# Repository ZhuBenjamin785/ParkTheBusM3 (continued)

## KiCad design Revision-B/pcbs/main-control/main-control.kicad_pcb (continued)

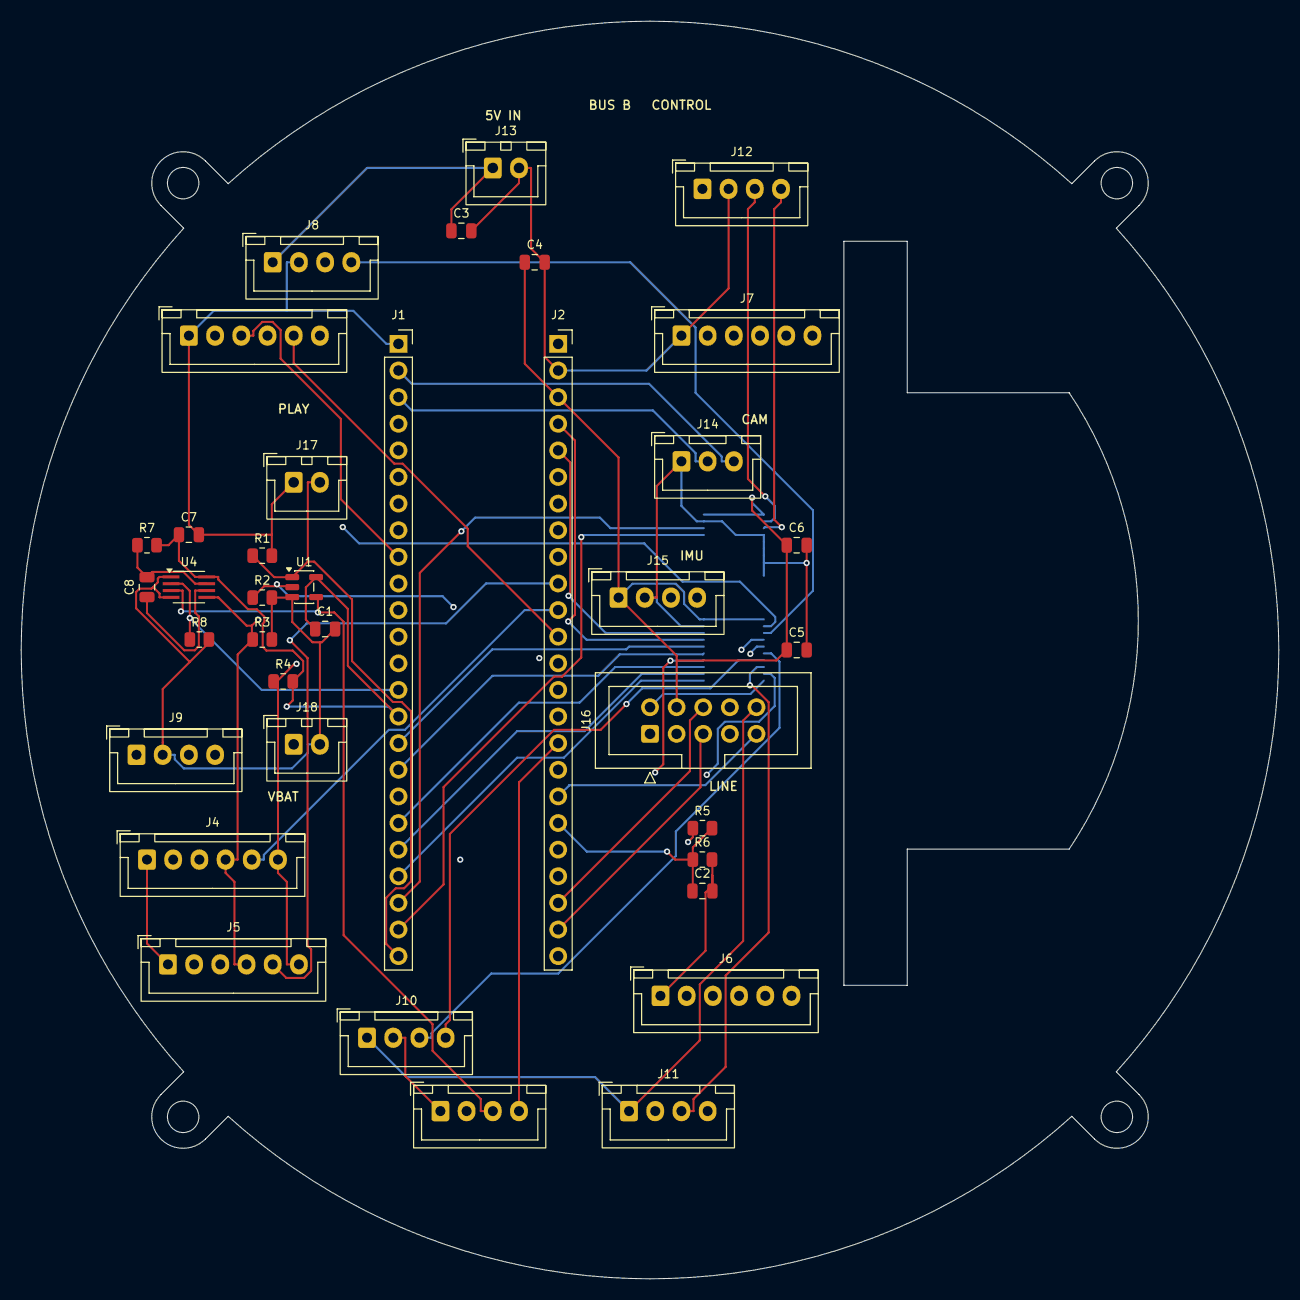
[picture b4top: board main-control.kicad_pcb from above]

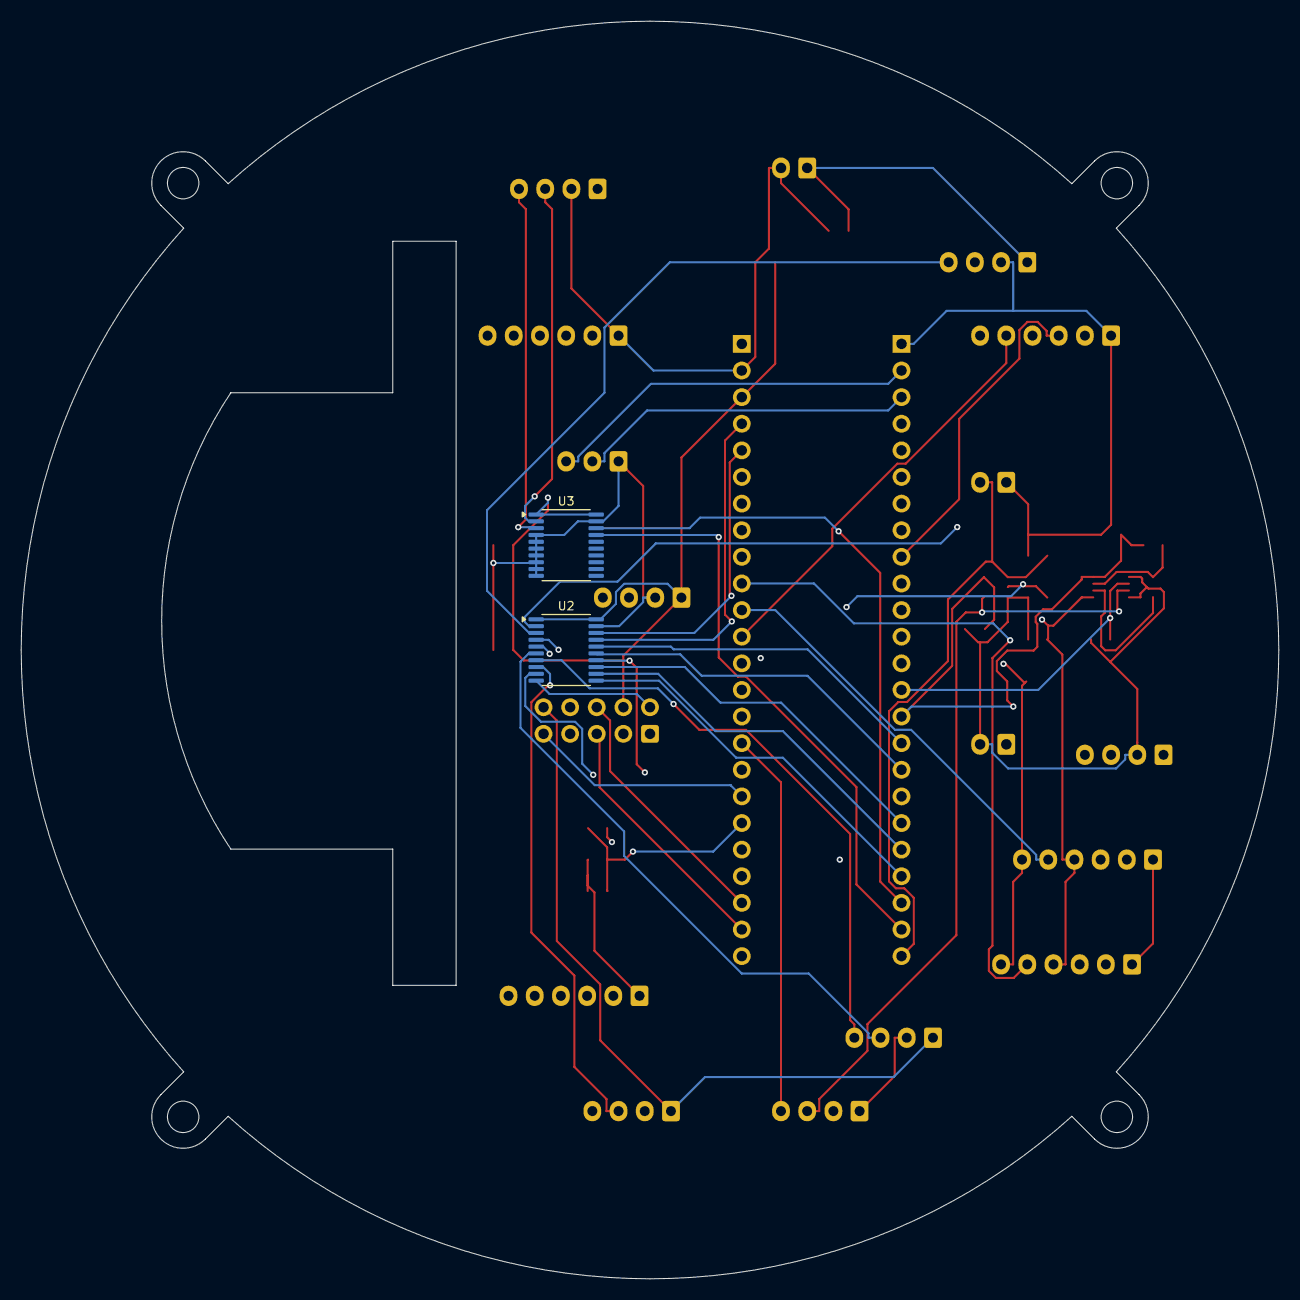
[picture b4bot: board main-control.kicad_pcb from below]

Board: 4 copper layers, 120.0 x 120.0 mm, 43 parts (2 on the bottom side), 59 nets.

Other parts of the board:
H1, H2, H3, H4: NPTH 3.0

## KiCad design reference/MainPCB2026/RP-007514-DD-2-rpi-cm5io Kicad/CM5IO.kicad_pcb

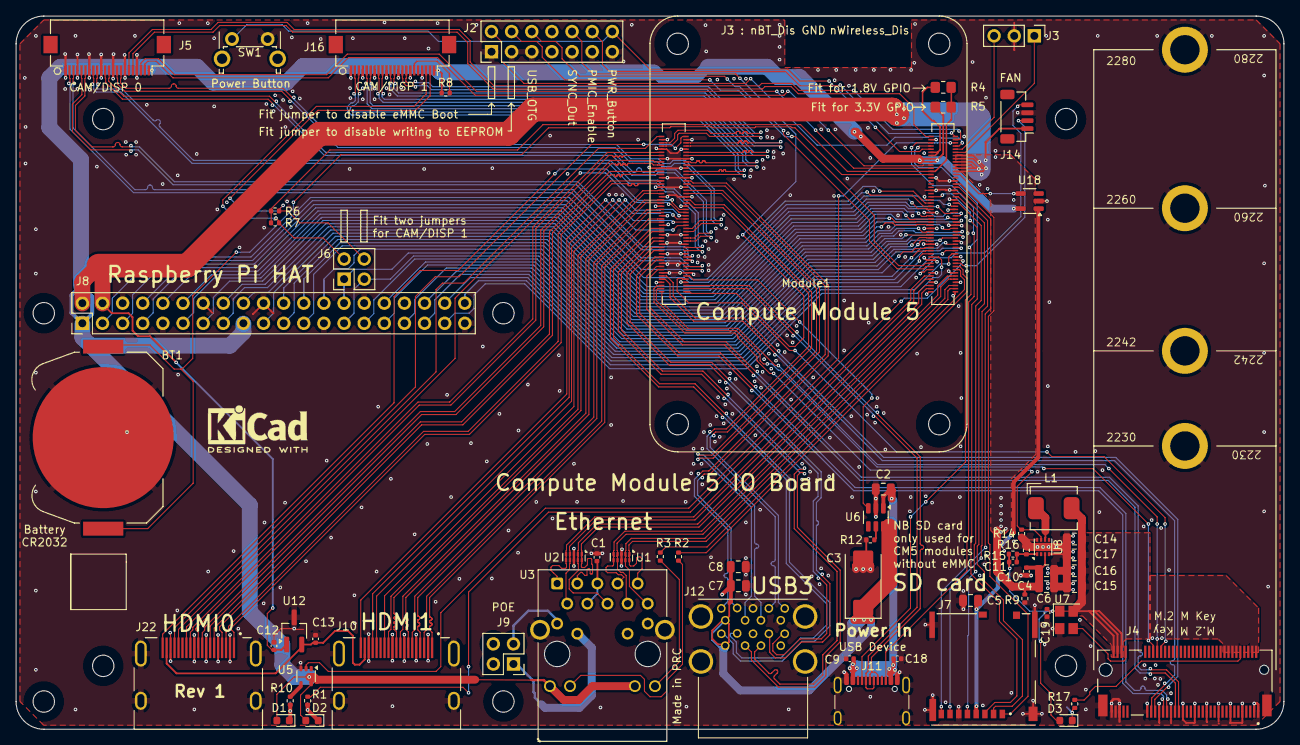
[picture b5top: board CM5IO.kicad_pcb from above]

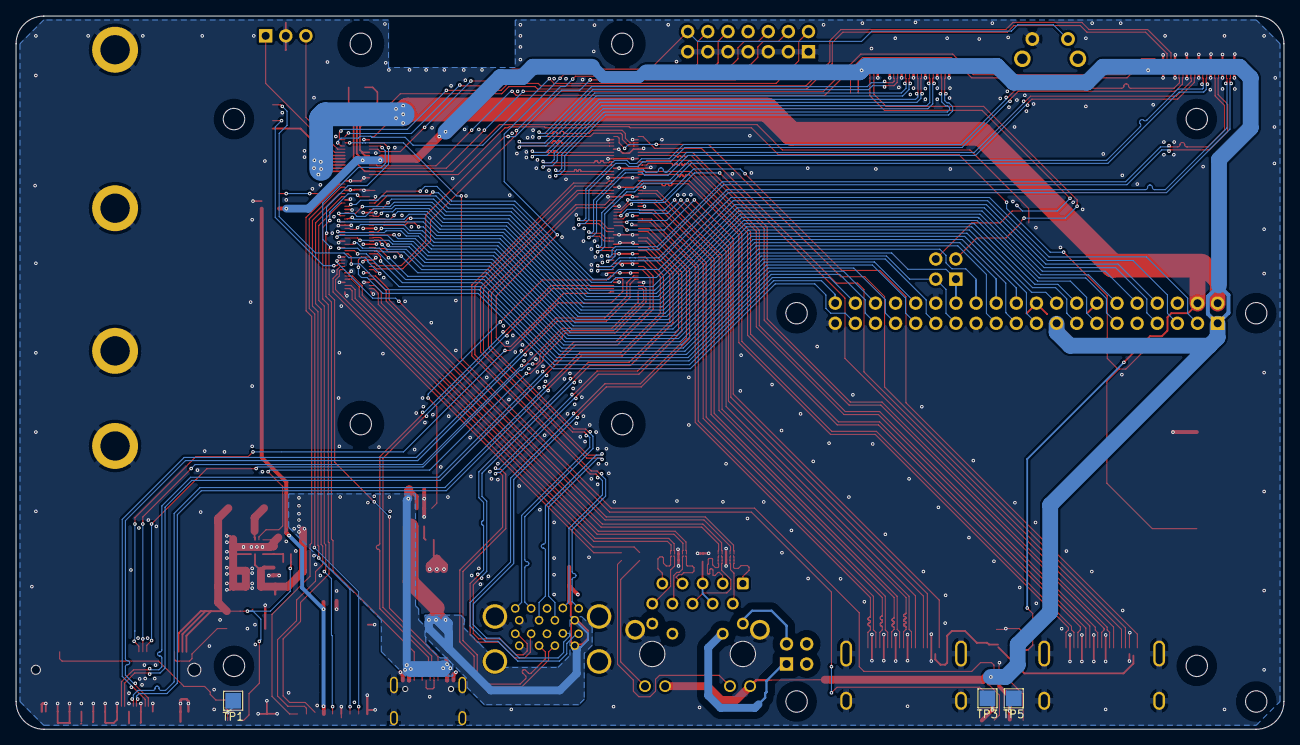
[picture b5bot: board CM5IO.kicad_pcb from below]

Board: 4 copper layers, 160.0 x 90.0 mm, 76 parts (3 on the bottom side), 161 nets.

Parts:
BT1: Battery_Cell; BatteryHolder_Keystone_3034_1x20mm
C1, C9, C10, C12, C13, C18, C19: 100n; C_0402_1005Metric
C2, C4, C5, C6, C7, C8, C14, C15, C16, C17: 10u; C_0805_2012Metric
C3: 100uF; CP_EIA-7343-31_Kemet-D
C11: 4.7nF; C_0402_1005Metric
D1: LED Red; LED_0603_1608Metric
D2, D3: LED Green; LED_0603_1608Metric
H1, H2, H3, H4, H5, H6, H7, H8: MountingHole; MountingHole_2.7mm_M2.5_DIN965
J2: Conn_02x07_Odd_Even; PinHeader_2x07_P2.54mm_Vertical
J3: Conn_01x03; PinHeader_1x03_P2.54mm_Vertical
J4: Bus_M.2_Socket_M; M.2 M Key socket
J5, J16: Conn_01x22_Female; Hirose_FH12-22S-0.5SH_1x22-1MP_P0.50mm_Horizontal
J6, J9: THD-02-R; PinHeader_2x02_P2.54mm_Vertical
J7: Micro_SD_Card_Det; SDCARD_MOLEX_503398-1892
J8: THD-20-R; PinHeader_2x20_P2.54mm_Vertical
J10, J22: 690-019-298-412; EDAC 690-019-298-412
J11: USB_C_Receptacle_USB2.0; USB_C_Receptacle_GCT_USB4105-xx-A_16P_TopMnt_Horizontal
J12: USB3_A; MTCONN_UBAF30-D2011
J14: JST_SHBM04B-SRSS-TB; JST_SH_BM04B-SRSS-TB_1x04-1MP_P1.00mm_Vertical
L1: 2.2uH; L_Bourns_SRP5030CC
Module1: ComputeModule5-CM5; Raspberry-Pi-5-Compute-Module
R1, R10, R17: 1k; R_0402_1005Metric
R2, R3: 470R; R_0402_1005Metric
R4: nf; R_0805_2012Metric_Pad1.20x1.40mm_HandSolder
R5: 0R; R_0805_2012Metric_Pad1.20x1.40mm_HandSolder
R6, R7, R8, R9, R16: 2.2K 1%; R_0402_1005Metric
R12: 15K 1%; R_0402_1005Metric
R14: 100K 1%; R_0402_1005Metric
R15: 10K 1%; R_0402_1005Metric
SW1: Right angle Tact button; SW_Tactile_SPST_Angled_PTS645Vx58-2LFS
TP1, TP3, TP5: TestPoint; TestPoint_Pad_2.0x2.0mm
U1, U2: TPD4EUSB30; USON-10_2.5x1.0mm_P0.5mm
U3: MagJack-A70-112-331N126; TRJG0926HENL
U5: 74LVC1G07SE-7; SOT-353_SC-70-5
U6: AP22653W6; SOT-23-6
U7: ASEK-32.768KHZ-L-R-T; Crystal_SMD_3225-4Pin_3.2x2.5mm
U8: AP3441SHE-7B; DFN-8-1EP_2x2mm_P0.5mm_EP1.05x1.75mm
U12: RT9742SNGV; TSOT-23_HandSoldering
U18: RT9742GGJ5; SOT-23-5
logo1: KiCad-Logo2_5mm_SilkScreen

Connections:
/+3.3v: D1.2 (A), D2.2 (A), J5.22, J8.1, J8.17, J16.22, Module1.84 (+3.3v_(Output)), Module1.86 (+3.3v_(Output)), R5.1, R8.1, U3.15 (LEDY_A), U3.17 (LEDG_A), U5.5 (VCC), U18.5 (IN)
/+5v: C2.1, C4.1, C6.1, C9.1, C10.1, C12.1, C18.1, J8.2, J8.4, J11.A4 (VBUS), J11.A9 (VBUS), J11.B4 (VBUS), J11.B9 (VBUS), J14.1, Module1.77 (+5v_(Input)), Module1.79 (+5v_(Input)), Module1.81 (+5v_(Input)), Module1.83 (+5v_(Input)), Module1.85 (+5v_(Input)), Module1.87 (+5v_(Input)), R9.1, U6.1 (IN), U8.3 (VIN), U12.1 (IN)
/CC1: J11.A5 (CC1), Module1.94 (CC1)
/CC2: J11.B5 (CC2), Module1.96 (CC2)
/CM5_GPIO ( Ethernet, GPIO, SDCARD)/+1.8v: Module1.88 (+1.8v_(Output)), Module1.90 (+1.8v_(Output)), R4.1
/CM5_GPIO ( Ethernet, GPIO, SDCARD)/BT_nDis: J3.3, Module1.91 (BT_nDisable)
/CM5_GPIO ( Ethernet, GPIO, SDCARD)/CAM_GPIO0: J5.17, Module1.97 (CAM_GPIO0)
/CM5_GPIO ( Ethernet, GPIO, SDCARD)/CAM_GPIO1: J5.18, Module1.100 (CAM_GPIO1)
/CM5_GPIO ( Ethernet, GPIO, SDCARD)/EEPROM_nWP: J2.4, Module1.20 (EEPROM_nWP)
/CM5_GPIO ( Ethernet, GPIO, SDCARD)/ETH_LEDG: Module1.17 (Ethernet_nLED2(3.3v)), R2.2
/CM5_GPIO ( Ethernet, GPIO, SDCARD)/ETH_LEDY: Module1.15 (Ethernet_nLED3(3.3v)), R3.2
/CM5_GPIO ( Ethernet, GPIO, SDCARD)/GPIO2: J8.3, Module1.58 (GPIO2)
/CM5_GPIO ( Ethernet, GPIO, SDCARD)/GPIO3: J8.5, Module1.56 (GPIO3)
/CM5_GPIO ( Ethernet, GPIO, SDCARD)/GPIO4: J8.7, Module1.54 (GPIO4)
/CM5_GPIO ( Ethernet, GPIO, SDCARD)/GPIO5: J8.29, Module1.34 (GPIO5)
/CM5_GPIO ( Ethernet, GPIO, SDCARD)/GPIO6: J8.31, Module1.30 (GPIO6)
/CM5_GPIO ( Ethernet, GPIO, SDCARD)/GPIO7: J8.26, Module1.37 (GPIO7)
/CM5_GPIO ( Ethernet, GPIO, SDCARD)/GPIO8: J8.24, Module1.39 (GPIO8)
/CM5_GPIO ( Ethernet, GPIO, SDCARD)/GPIO9: J8.21, Module1.40 (GPIO9)
/CM5_GPIO ( Ethernet, GPIO, SDCARD)/GPIO10: J8.19, Module1.44 (GPIO10)
/CM5_GPIO ( Ethernet, GPIO, SDCARD)/GPIO11: J8.23, Module1.38 (GPIO11)
/CM5_GPIO ( Ethernet, GPIO, SDCARD)/GPIO12: J8.32, Module1.31 (GPIO12)
/CM5_GPIO ( Ethernet, GPIO, SDCARD)/GPIO13: J8.33, Module1.28 (GPIO13)
/CM5_GPIO ( Ethernet, GPIO, SDCARD)/GPIO14: J8.8, Module1.55 (GPIO14)
/CM5_GPIO ( Ethernet, GPIO, SDCARD)/GPIO15: J8.10, Module1.51 (GPIO15)
/CM5_GPIO ( Ethernet, GPIO, SDCARD)/GPIO16: J8.36, Module1.29 (GPIO16)
/CM5_GPIO ( Ethernet, GPIO, SDCARD)/GPIO17: J8.11, Module1.50 (GPIO17)
/CM5_GPIO ( Ethernet, GPIO, SDCARD)/GPIO18: J8.12, Module1.49 (GPIO18)
/CM5_GPIO ( Ethernet, GPIO, SDCARD)/GPIO19: J8.35, Module1.26 (GPIO19)
/CM5_GPIO ( Ethernet, GPIO, SDCARD)/GPIO20: J8.38, Module1.27 (GPIO20)
/CM5_GPIO ( Ethernet, GPIO, SDCARD)/GPIO21: J8.40, Module1.25 (GPIO21)
/CM5_GPIO ( Ethernet, GPIO, SDCARD)/GPIO22: J8.15, Module1.46 (GPIO22)
/CM5_GPIO ( Ethernet, GPIO, SDCARD)/GPIO23: J8.16, Module1.47 (GPIO23)
/CM5_GPIO ( Ethernet, GPIO, SDCARD)/GPIO24: J8.18, Module1.45 (GPIO24)
/CM5_GPIO ( Ethernet, GPIO, SDCARD)/GPIO25: J8.22, Module1.41 (GPIO25)
/CM5_GPIO ( Ethernet, GPIO, SDCARD)/GPIO26: J8.37, Module1.24 (GPIO26)
/CM5_GPIO ( Ethernet, GPIO, SDCARD)/GPIO27: J8.13, Module1.48 (GPIO27)
/CM5_GPIO ( Ethernet, GPIO, SDCARD)/GPIO_VREF: Module1.78 (GPIO_VREF(1.8v/3.3v_Input)), R4.2, R5.2, R6.1, R7.1
/CM5_GPIO ( Ethernet, GPIO, SDCARD)/ID_SC: J6.1, J8.28, Module1.35 (ID_SC)
/CM5_GPIO ( Ethernet, GPIO, SDCARD)/ID_SD: J6.3, J8.27, Module1.36 (ID_SD)
/CM5_GPIO ( Ethernet, GPIO, SDCARD)/PMIC_ENABLE: J2.12, Module1.99 (PMIC_ENABLE)
/CM5_GPIO ( Ethernet, GPIO, SDCARD)/PWM: J14.2, Module1.19 (FAN_PWM)
/CM5_GPIO ( Ethernet, GPIO, SDCARD)/PWR_BUT: J2.14, Module1.92 (PWR_BUT), SW1.1
/CM5_GPIO ( Ethernet, GPIO, SDCARD)/SD_CLK: J7.5 (CLK), Module1.57 (SD_CLK)
/CM5_GPIO ( Ethernet, GPIO, SDCARD)/SD_CMD: J7.3 (CMD), Module1.62 (SD_CMD)
/CM5_GPIO ( Ethernet, GPIO, SDCARD)/SD_DAT0: J7.7 (DAT0), Module1.63 (SD_DAT0)
/CM5_GPIO ( Ethernet, GPIO, SDCARD)/SD_DAT1: J7.8 (DAT1), Module1.67 (SD_DAT1)
/CM5_GPIO ( Ethernet, GPIO, SDCARD)/SD_DAT2: J7.1 (DAT2), Module1.69 (SD_DAT2)
/CM5_GPIO ( Ethernet, GPIO, SDCARD)/SD_DAT3: J7.2 (DAT3/CD), Module1.61 (SD_DAT3)
/CM5_GPIO ( Ethernet, GPIO, SDCARD)/SD_PWR: C5.1, J7.4 (VDD), U18.1 (OUT)
/CM5_GPIO ( Ethernet, GPIO, SDCARD)/SD_PWR_ON: Module1.75 (SD_PWR_ON), U18.4 (EN)
/CM5_GPIO ( Ethernet, GPIO, SDCARD)/SYNC_OUT: J2.6, Module1.18 (Ethernet_SYNC_OUT(1.8v))
/CM5_GPIO ( Ethernet, GPIO, SDCARD)/TACHO: J14.4, Module1.16 (FAN_TACHO)
/CM5_GPIO ( Ethernet, GPIO, SDCARD)/TR0_TAP: J9.3, U3.11 (VC1)
/CM5_GPIO ( Ethernet, GPIO, SDCARD)/TR1_TAP: J9.1, U3.12 (VC2)
/CM5_GPIO ( Ethernet, GPIO, SDCARD)/TR2_TAP: J9.2, U3.13 (VC3)
/CM5_GPIO ( Ethernet, GPIO, SDCARD)/TR3_TAP: J9.4, U3.14 (VC4)
/CM5_GPIO ( Ethernet, GPIO, SDCARD)/TRD0_N: Module1.10 (Ethernet_Pair0_N), U2.4 (D2+), U2.7, U3.2 (TRD0-)
/CM5_GPIO ( Ethernet, GPIO, SDCARD)/TRD0_P: Module1.12 (Ethernet_Pair0_P), U2.5 (D2-), U2.6, U3.1 (TRD0+)
/CM5_GPIO ( Ethernet, GPIO, SDCARD)/TRD1_N: Module1.6 (Ethernet_Pair1_N), U2.2 (D1-), U2.9, U3.6 (TRD1-)
/CM5_GPIO ( Ethernet, GPIO, SDCARD)/TRD1_P: Module1.4 (Ethernet_Pair1_P), U2.1 (D1+), U2.10, U3.3 (TRD1+)
/CM5_GPIO ( Ethernet, GPIO, SDCARD)/TRD2_N: Module1.9 (Ethernet_Pair2_N), U1.4 (D2+), U1.7, U3.8 (TRD2-)
/CM5_GPIO ( Ethernet, GPIO, SDCARD)/TRD2_P: Module1.11 (Ethernet_Pair2_P), U1.5 (D2-), U1.6, U3.7 (TRD2+)
/CM5_GPIO ( Ethernet, GPIO, SDCARD)/TRD3_N: Module1.5 (Ethernet_Pair3_N), U1.2 (D1-), U1.9, U3.10 (TRD3-)
/CM5_GPIO ( Ethernet, GPIO, SDCARD)/TRD3_P: Module1.3 (Ethernet_Pair3_P), U1.1 (D1+), U1.10, U3.9 (TRD3+)
/CM5_GPIO ( Ethernet, GPIO, SDCARD)/USBOTG: J2.10, Module1.101 (USB_OTG_ID)
/CM5_GPIO ( Ethernet, GPIO, SDCARD)/VBAT: BT1.1 (+), Module1.76 (VBAT)
/CM5_GPIO ( Ethernet, GPIO, SDCARD)/WL_nDis: J3.1, Module1.89 (WiFi_nDisable)
/CM5_GPIO ( Ethernet, GPIO, SDCARD)/nPWR_LED: Module1.95 (LED_nPWR), U5.2
/CM5_GPIO ( Ethernet, GPIO, SDCARD)/nRPIBOOT: J2.2, Module1.93 (nRPIBOOT)
/CM5_HighSpeed/DPHY0_C_N: J5.8, Module1.127 (DPHY0_C_N)
/CM5_HighSpeed/DPHY0_C_P: J5.9, Module1.129 (DPHY0_C_P)
/CM5_HighSpeed/DPHY0_D0_N: J5.2, Module1.115 (DPHY0_D0_N)
/CM5_HighSpeed/DPHY0_D0_P: J5.3, Module1.117 (DPHY0_D0_P)
/CM5_HighSpeed/DPHY0_D1_N: J5.5, Module1.121 (DPHY0_D1_N)
/CM5_HighSpeed/DPHY0_D1_P: J5.6, Module1.123 (DPHY0_D1_P)
/CM5_HighSpeed/DPHY0_D2_N: J5.11, Module1.133 (DPHY0_D2_N)
/CM5_HighSpeed/DPHY0_D2_P: J5.12, Module1.135 (DPHY0_D2_P)
/CM5_HighSpeed/DPHY0_D3_N: J5.14, Module1.139 (DPHY0_D3_N)
/CM5_HighSpeed/DPHY0_D3_P: J5.15, Module1.141 (DPHY0_D3_P)
/CM5_HighSpeed/DPHY1_C_N: J16.8, Module1.187 (DPHY1_C_N)
/CM5_HighSpeed/DPHY1_C_P: J16.9, Module1.189 (DPHY1_C_P)
/CM5_HighSpeed/DPHY1_D0_N: J16.2, Module1.175 (DPHY1_D0_N)
/CM5_HighSpeed/DPHY1_D0_P: J16.3, Module1.177 (DPHY1_D0_P)
/CM5_HighSpeed/DPHY1_D1_N: J16.5, Module1.181 (DPHY1_D1_N)
/CM5_HighSpeed/DPHY1_D1_P: J16.6, Module1.183 (DPHY1_D1_P)
/CM5_HighSpeed/DPHY1_D2_N: J16.11, Module1.193 (DPHY1_D2_N)
/CM5_HighSpeed/DPHY1_D2_P: J16.12, Module1.195 (DPHY1_D2_P)
/CM5_HighSpeed/DPHY1_D3_N: J16.14, Module1.194 (DPHY1_D3_N)
/CM5_HighSpeed/DPHY1_D3_P: J16.15, Module1.196 (DPHY1_D3_P)
/CM5_HighSpeed/HDMI0_CEC: J22.13 (CEC), Module1.151 (HDMI0_CEC)
/CM5_HighSpeed/HDMI0_CK_N: J22.12 (CK-), Module1.190 (HDMI0_CLK_N)
/CM5_HighSpeed/HDMI0_CK_P: J22.10 (CK+), Module1.188 (HDMI0_CLK_P)
/CM5_HighSpeed/HDMI0_D0_N: J22.9 (D0-), Module1.184 (HDMI0_TX0_N)
/CM5_HighSpeed/HDMI0_D0_P: J22.7 (D0+), Module1.182 (HDMI0_TX0_P)
/CM5_HighSpeed/HDMI0_D1_N: J22.6 (D1-), Module1.178 (HDMI0_TX1_N)
/CM5_HighSpeed/HDMI0_D1_P: J22.4 (D1+), Module1.176 (HDMI0_TX1_P)
/CM5_HighSpeed/HDMI0_D2_N: J22.3 (D2-), Module1.172 (HDMI0_TX2_N)
/CM5_HighSpeed/HDMI0_D2_P: J22.1 (D2+), Module1.170 (HDMI0_TX2_P)
/CM5_HighSpeed/HDMI0_HOTPLUG: J22.19 (HPD/HEAC-), Module1.153 (HDMI0_HOTPLUG)
/CM5_HighSpeed/HDMI0_SCL: J22.15 (SCL), Module1.200 (HDMI0_SCL)
/CM5_HighSpeed/HDMI0_SDA: J22.16 (SDA), Module1.199 (HDMI0_SDA)
/CM5_HighSpeed/HDMI1_CEC: J10.13 (CEC), Module1.149 (HDMI1_CEC)
/CM5_HighSpeed/HDMI1_CK_N: J10.12 (CK-), Module1.166 (HDMI1_CLK_N)
/CM5_HighSpeed/HDMI1_CK_P: J10.10 (CK+), Module1.164 (HDMI1_CLK_P)
/CM5_HighSpeed/HDMI1_D0_N: J10.9 (D0-), Module1.160 (HDMI1_TX0_N)
/CM5_HighSpeed/HDMI1_D0_P: J10.7 (D0+), Module1.158 (HDMI1_TX0_P)
/CM5_HighSpeed/HDMI1_D1_N: J10.6 (D1-), Module1.154 (HDMI1_TX1_N)
/CM5_HighSpeed/HDMI1_D1_P: J10.4 (D1+), Module1.152 (HDMI1_TX1_P)
/CM5_HighSpeed/HDMI1_D2_N: J10.3 (D2-), Module1.148 (HDMI1_TX2_N)
/CM5_HighSpeed/HDMI1_D2_P: J10.1 (D2+), Module1.146 (HDMI1_TX2_P)
/CM5_HighSpeed/HDMI1_HOTPLUG: J10.19 (HPD/HEAC-), Module1.143 (HDMI1_HOTPLUG)
/CM5_HighSpeed/HDMI1_SCL: J10.15 (SCL), Module1.147 (HDMI1_SCL)
/CM5_HighSpeed/HDMI1_SDA: J10.16 (SDA), Module1.145 (HDMI1_SDA)
/CM5_HighSpeed/HDMI_5v: C13.1, J10.18 (+5V), J22.18 (+5V), U12.2 (OUT)
/CM5_HighSpeed/PCIE_CLK_N: J4.53 (REFCLKn), Module1.112 (PCIe_CLK_N)
/CM5_HighSpeed/PCIE_CLK_P: J4.55 (REFCLKp), Module1.110 (PCIe_CLK_P)
/CM5_HighSpeed/PCIE_PWR_EN: Module1.106 (PCIE_PWR_EN), R14.1, U8.7 (EN)
/CM5_HighSpeed/PCIE_RX_N: J4.43 (PETp0), Module1.118 (PCIe_RX_N)
/CM5_HighSpeed/PCIE_RX_P: J4.41 (PETn0), Module1.116 (PCIe_RX_P)
/CM5_HighSpeed/PCIE_TX_N: J4.49 (PERp0), Module1.124 (PCIe_TX_N)
/CM5_HighSpeed/PCIE_TX_P: J4.47 (PERn0), Module1.122 (PCIe_TX_P)
/CM5_HighSpeed/PCIE_nCLKREQ: J4.52 (~CLKREQ), Module1.102 (PCIe_nCLKREQ)
/CM5_HighSpeed/PCIE_nRST: J4.50 (~PERST), Module1.109 (PCIe_nRST)
/CM5_HighSpeed/PCIE_nWAKE: J4.54 (~PEWAKE), Module1.104 (PCIE_nWAKE)
/CM5_HighSpeed/SCL0: J5.20, Module1.80 (SCL0)
/CM5_HighSpeed/SCL1: J6.2, J16.20, R7.2
/CM5_HighSpeed/SDA0: J5.21, Module1.82 (SDA0)
/CM5_HighSpeed/SDA1: J6.4, J16.21, R6.2
/CM5_HighSpeed/USB3-0-D_N: J12.A2 (D-), Module1.136 (USB3-0-D_N)
/CM5_HighSpeed/USB3-0-D_P: J12.A3 (D+), Module1.134 (USB3-0-D_P)
/CM5_HighSpeed/USB3-0-RX_N: J12.A6 (SSRX+), Module1.128 (USB3-0-RX_N)
/CM5_HighSpeed/USB3-0-RX_P: J12.A5 (SSRX-), Module1.130 (USB3-0-RX_P)
/CM5_HighSpeed/USB3-0-TX_N: J12.A9 (SSTX+), Module1.140 (USB3-0-TX_N)
/CM5_HighSpeed/USB3-0-TX_P: J12.A8 (SSTX-), Module1.142 (USB3-0-TX_P)
/CM5_HighSpeed/USB3-1-D_N: J12.B2 (D-), Module1.165 (USB3-1-D_N)
/CM5_HighSpeed/USB3-1-D_P: J12.B3 (D+), Module1.163 (USB3-1-D_P)
/CM5_HighSpeed/USB3-1-RX_N: J12.B6 (SSRX+), Module1.157 (USB3-1-RX_N)
/CM5_HighSpeed/USB3-1-RX_P: J12.B5 (SSRX-), Module1.159 (USB3-1-RX_P)
/CM5_HighSpeed/USB3-1-TX_N: J12.B9 (SSTX+), Module1.169 (USB3-1-TX_N)
/CM5_HighSpeed/USB3-1-TX_P: J12.B8 (SSTX-), Module1.171 (USB3-1-TX_P)
/CM5_HighSpeed/VBUS: C3.1, C7.1, C8.1, J12.A1 (VBUS), J12.B1 (VBUS), U6.6 (OUT)
/CM5_HighSpeed/VBUS_EN: Module1.111 (VBUS_EN), U6.3 (EN)
/PCIe-M2/FB: C11.2, R15.2, R16.1, U8.1 (FB)
/PCIe-M2/M2_3v3: C11.1, C14.1, C15.1, C16.1, C17.1, C19.1, D3.2 (A), J4.2 (3.3V), J4.4 (3.3V), J4.12 (3.3V), J4.14 (3.3V), J4.16 (3.3V), J4.18 (3.3V), J4.70 (3.3V), J4.72 (3.3V), J4.74 (3.3V), L1.2, R15.1, U7.1 (EN), U7.4 (VDD)
/USB2_N: J11.A7 (D-), J11.B7 (D-), Module1.103 (USB2_N)
/USB2_P: J11.A6 (D+), J11.B6 (D+), Module1.105 (USB2_P)
GND: BT1.2 (-), C1.2, C2.2, C3.2, C4.2, C5.2, C6.2, C7.2, C8.2, C9.2, C10.2, C12.2, C13.2, C14.2, C15.2, C16.2, C17.2, C18.2, C19.2, J2.1, J2.3, J2.5, J2.7, J2.9, J2.11, J2.13, J3.2, J4.1 (GND), J4.3 (GND), J4.9 (GND), J4.15 (GND), J4.21 (GND), J4.27 (GND), J4.33 (GND), J4.39 (GND), J4.45 (GND), J4.51 (GND), J4.57 (GND), J4.71 (GND), J4.73 (GND), J4.75 (GND), J4.M1 (GND2230), J4.M2 (GND2242), J4.M3 (GND2260), J4.M4 (GND2280), J4.S1, J4.S2, J5.1, J5.4, J5.7, J5.10, J5.13, J5.16, J5.19, J7.6 (VSS), J7.11 (SHIELD), J8.6, J8.9, J8.14, J8.20, J8.25, J8.30, J8.34, J8.39, J10.2 (D2S), J10.5 (D1S), J10.8 (D0S), J10.11 (CKS), J10.17 (GND), J10.SH1 (SH), J10.SH2 (SH), J10.SH3 (SH), J10.SH4 (SH), J11.A1 (GND), J11.A12 (GND), J11.B1 (GND), J11.B12 (GND), J11.S1 (SHIELD), J12.10 (SHIELD), J12.A4 (GND), J12.A7 (DRAIN), J12.B4 (GND), J12.B7 (DRAIN), J14.3, J16.1, J16.4, J16.7, J16.10, J16.13, J16.16, J16.19, J22.2 (D2S), J22.5 (D1S), J22.8 (D0S), J22.11 (CKS), J22.17 (GND), J22.SH1 (SH), J22.SH2 (SH), J22.SH3 (SH), J22.SH4 (SH), Module1.1 (GND), Module1.2 (GND), Module1.7 (GND), Module1.8 (GND), Module1.13 (GND), Module1.14 (GND), Module1.22 (GND), Module1.23 (GND), Module1.32 (GND), Module1.33 (GND), Module1.42 (GND), Module1.43 (GND), Module1.52 (GND), Module1.53 (GND), Module1.59 (GND), Module1.60 (GND), Module1.65 (GND), Module1.66 (GND), Module1.71 (GND), Module1.74 (GND), Module1.98 (GND), Module1.107 (GND), Module1.108 (GND), Module1.113 (GND), Module1.114 (GND), Module1.119 (GND), Module1.120 (GND), Module1.125 (GND), Module1.126 (GND), Module1.131 (GND), Module1.132 (GND), Module1.137 (GND), Module1.138 (GND), Module1.144 (GND), Module1.150 (GND), Module1.155 (GND), Module1.156 (GND), Module1.161 (GND), Module1.162 (GND), Module1.167 (GND), Module1.168 (GND), Module1.173 (GND), Module1.174 (GND), Module1.179 (GND), Module1.180 (GND), Module1.185 (GND), Module1.186 (GND), Module1.191 (GND), Module1.192 (GND), Module1.197 (GND), Module1.198 (GND), R9.2, R12.2, R14.2, R16.2, SW1.2, U1.3 (GND), U1.8 (GND), U2.3 (GND), U2.8 (GND), U3.19 (SHIELD), U3.20 (SHIELD), U5.3 (GND), U6.2 (GND), U7.2 (GND), U8.4 (PGND), U8.8 (SGND), U8.9 (PAD), U12.3 (GND), U18.2 (GND)
unnamed: C1.1, U3.4 (CT), U3.5 (CT)
unnamed: D1.1 (K), R10.1, TP5.1
unnamed: D2.1 (K), R1.1, TP3.1
unnamed: D3.1 (K), R17.1, TP1.1
unnamed: J4.10 (DAS/~DSS/~LED1), R17.2
unnamed: J4.68 (SUSCLK), U7.3 (Out)
unnamed: J16.17, R8.2
unnamed: Module1.21 (LED_nACT), R1.2
unnamed: R10.2, U5.4
unnamed: R3.1, U3.18 (LEDG_K)
unnamed: R2.1, U3.16 (LEDY_K)
unnamed: R12.1, U6.5 (ILIM)
unnamed: L1.1, U8.6 (LX)

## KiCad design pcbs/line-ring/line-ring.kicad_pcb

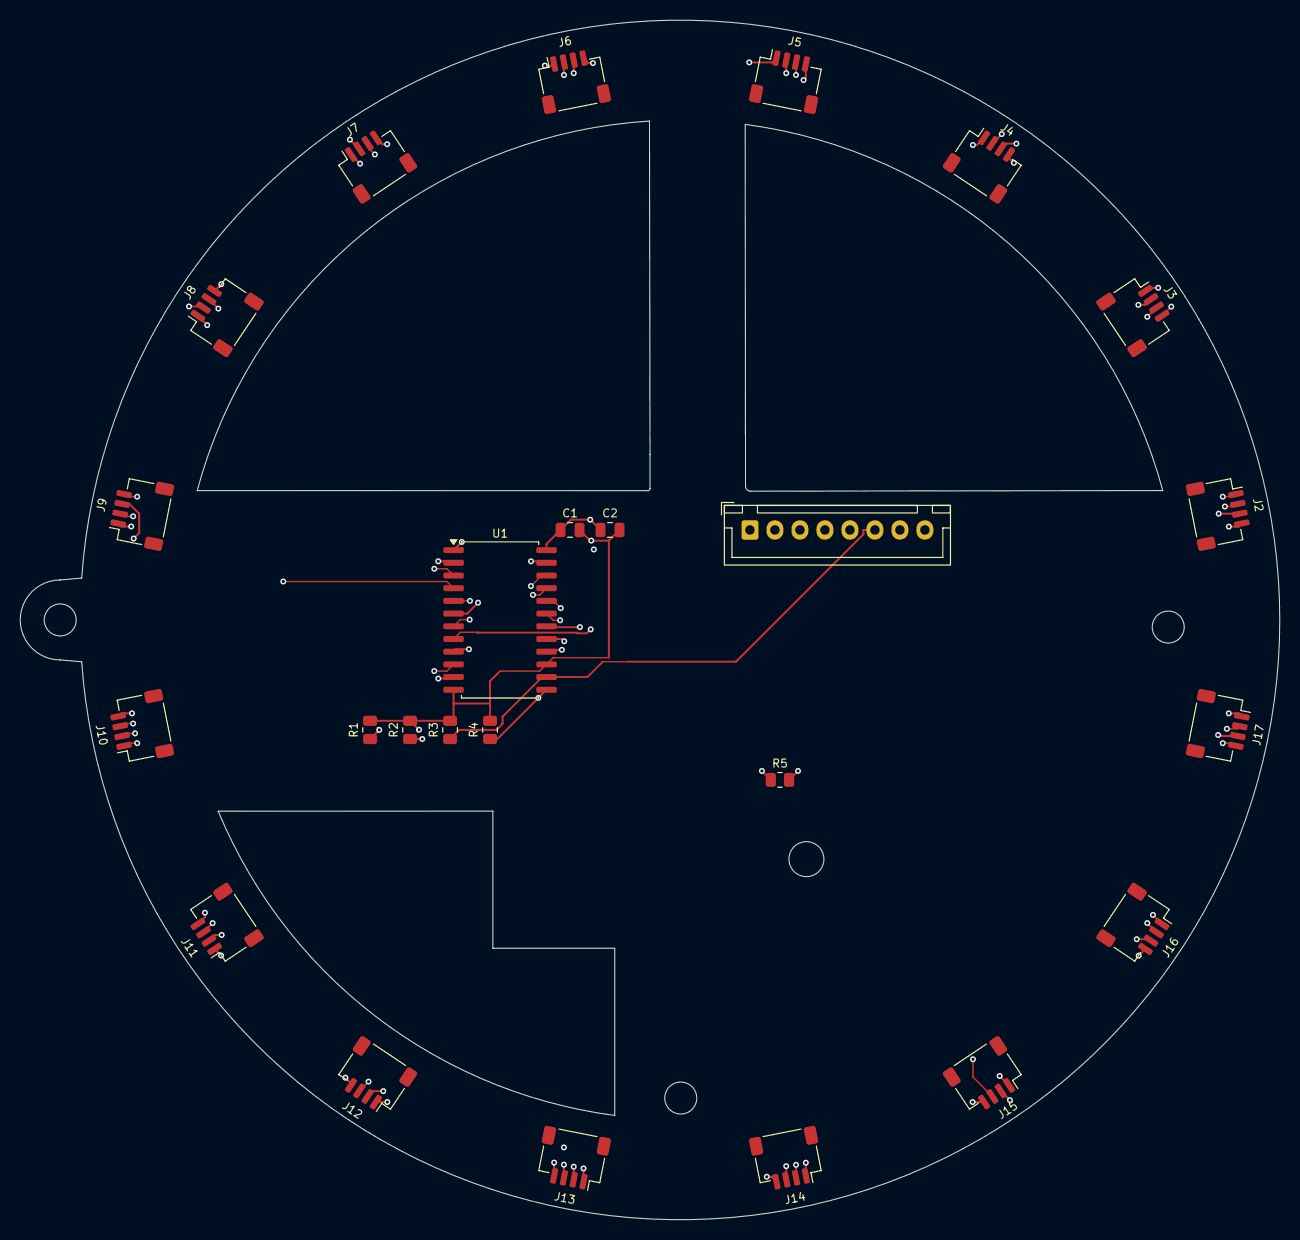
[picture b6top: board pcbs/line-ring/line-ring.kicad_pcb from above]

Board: 4 copper layers, 126.0 x 120.0 mm, 29 parts (0 on the bottom side), 24 nets.

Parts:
C1: 100n 16V; C_0805_2012Metric
C2: 10u 10V; C_0805_2012Metric
H1, H2, H3: NPTH 3.2
H4: NPTH 3.5
J1: MAIN HARNESS; JST_XH_B8B-XH-A_1x08_P2.50mm_Vertical
J2: QTRX 0; JST_SH_SM04B-SRSS-TB_1x04-1MP_P1.00mm_Horizontal
J3: QTRX 1; JST_SH_SM04B-SRSS-TB_1x04-1MP_P1.00mm_Horizontal
J4: QTRX 2; JST_SH_SM04B-SRSS-TB_1x04-1MP_P1.00mm_Horizontal
J5: QTRX 3; JST_SH_SM04B-SRSS-TB_1x04-1MP_P1.00mm_Horizontal
J6: QTRX 4; JST_SH_SM04B-SRSS-TB_1x04-1MP_P1.00mm_Horizontal
J7: QTRX 5; JST_SH_SM04B-SRSS-TB_1x04-1MP_P1.00mm_Horizontal
J8: QTRX 6; JST_SH_SM04B-SRSS-TB_1x04-1MP_P1.00mm_Horizontal
J9: QTRX 7; JST_SH_SM04B-SRSS-TB_1x04-1MP_P1.00mm_Horizontal
J10: QTRX 8; JST_SH_SM04B-SRSS-TB_1x04-1MP_P1.00mm_Horizontal
J11: QTRX 9; JST_SH_SM04B-SRSS-TB_1x04-1MP_P1.00mm_Horizontal
J12: QTRX 10; JST_SH_SM04B-SRSS-TB_1x04-1MP_P1.00mm_Horizontal
J13: QTRX 11; JST_SH_SM04B-SRSS-TB_1x04-1MP_P1.00mm_Horizontal
J14: QTRX 12; JST_SH_SM04B-SRSS-TB_1x04-1MP_P1.00mm_Horizontal
J15: QTRX 13; JST_SH_SM04B-SRSS-TB_1x04-1MP_P1.00mm_Horizontal
J16: QTRX 14; JST_SH_SM04B-SRSS-TB_1x04-1MP_P1.00mm_Horizontal
J17: QTRX 15; JST_SH_SM04B-SRSS-TB_1x04-1MP_P1.00mm_Horizontal
R1, R2, R3, R4: 100k; R_0805_2012Metric
R5: 10k; R_0805_2012Metric
U1: CD74HC4067M; SOIC-24W_7.5x15.4mm_P1.27mm

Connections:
3V3: C1.1, C2.1, J1.1, J2.2, J3.2, J4.2, J5.2, J6.2, J7.2, J8.2, J9.2, J10.2, J11.2, J12.2, J13.2, J14.2, J15.2, J16.2, J17.2, R5.2, U1.24
GND: C1.2, C2.2, J1.2, J2.3, J3.3, J4.3, J5.3, J6.3, J7.3, J8.3, J9.3, J10.3, J11.3, J12.3, J13.3, J14.3, J15.3, J16.3, J17.3, R1.2, R2.2, R3.2, R4.2, U1.12, U1.15
LINE_ANALOG: J1.3, U1.1
LINE_CTRL: J1.8, J2.4, J3.4, J4.4, J5.4, J6.4, J7.4, J8.4, J9.4, J10.4, J11.4, J12.4, J13.4, J14.4, J15.4, J16.4, J17.4, R5.1
LINE_S0: J1.4, R1.1, U1.10
LINE_S1: J1.5, R2.1, U1.11
LINE_S2: J1.6, R3.1, U1.14
LINE_S3: J1.7, R4.1, U1.13
SENSE_0: J2.1, U1.9
SENSE_1: J3.1, U1.8
SENSE_2: J4.1, U1.7
SENSE_3: J5.1, U1.6
SENSE_4: J6.1, U1.5
SENSE_5: J7.1, U1.4
SENSE_6: J8.1, U1.3
SENSE_7: J9.1, U1.2
SENSE_8: J10.1, U1.23
SENSE_9: J11.1, U1.22
SENSE_10: J12.1, U1.21
SENSE_11: J13.1, U1.20
SENSE_12: J14.1, U1.19
SENSE_13: J15.1, U1.18
SENSE_14: J16.1, U1.17
SENSE_15: J17.1, U1.16

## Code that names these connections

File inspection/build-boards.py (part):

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# Teensy header sockets use manufacturer row sequence (top view, USB at top).
left=['GND']+[str(i) for i in range(13)]+['3V3']+[str(i) for i in range(24,33)]
right=['5V','GND','3V3']+[str(i) for i in range(23,12,-1)]+['GND']+[str(i) for i in range(41,32,-1)]
gpio={0:'CAM_TX',1:'CAM_RX',12:'AUX_PWM',13:'DRIVER_FAULT',14:'LINE_ANALOG',18:'SDA',19:'SCL',32:'REF_PLAY',33:'MCU_ENABLE',38:'BAT_SENSE',39:'LINE_CTRL',40:'AUX_A16',41:'AUX_A17'}
for i in range(5):gpio[2+i]=f'M{i+1}_PWM';gpio[7+i]=f'M{i+1}_DIR';gpio[[15,16,17,20,21][i]]=f'M{i+1}_CS';gpio[22+2*i]=f'M{i+1}_EA';gpio[23+2*i]=f'M{i+1}_EB'
for i in range(4):gpio[34+i]=f'LINE_S{i}'
for ref,row,x in [('J1',left,-24),('J2',right,-8.76)]:
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m.conn('J14','OPENMV UART ONLY',3,18,['GND','CAM_RX','CAM_TX'])
m.conn('J15','IMU 3V3',-3,5,['3V3','GND','SDA','SCL'])
m.conn('J16','LINE HARNESS',-4,-8,['3V3','GND','LINE_ANALOG','LINE_S0','LINE_S1','LINE_S2','LINE_S3','LINE_CTRL'])
m.conn('J17','REFEREE GPIO',-34,16,['GND','REF_PLAY'])
m.conn('J18','BATTERY MONITOR',-34,-9,['VBAT_SENSE_IN','GND'])
m.conn('J19','AUX LOGIC ONLY',-20,-44,['GND','AUX_PWM','AUX_A16','AUX_A17'])
m.add('U1','SN74LVC1G08DBVR','Package_TO_SOT_SMD:SOT-23-5',-33,6,{'1':('A','REF_PLAY'),'2':('B','MCU_ENABLE'),'3':('GND','GND'),'4':('Y','DRIVE_ENABLE'),'5':('VCC','3V3')},types={'1':'input','2':'input','4':'output'})
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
